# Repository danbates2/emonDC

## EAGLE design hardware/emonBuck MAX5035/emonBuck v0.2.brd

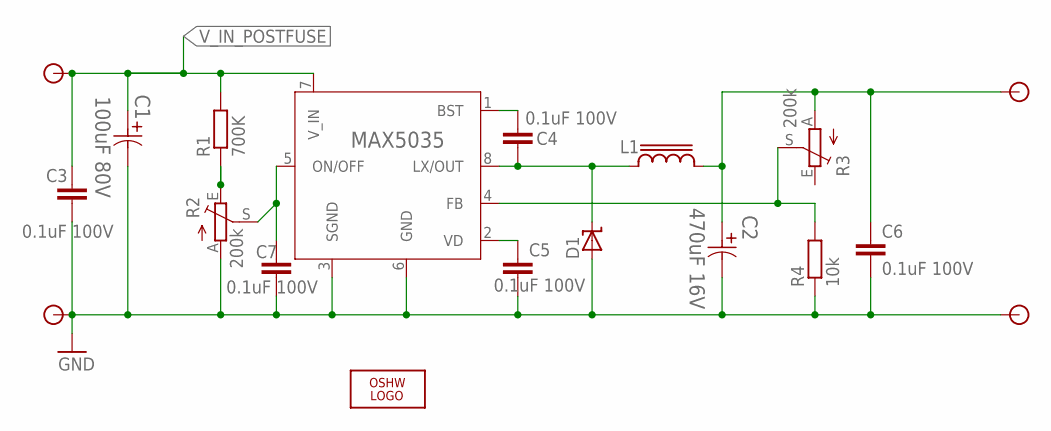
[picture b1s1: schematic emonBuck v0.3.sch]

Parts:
C1: 100uF 80V; CAPAE1350X1400N
C2: 470uF 16V; CAPAE830X1050N
C3, C4, C5, C6, C7: 0.1uF 100V; C0603
D1: MBRS1100T3G; SMB_1; MPN MBRS1100T3G
L1: SRR1208; SSR1208; MPN SRR1208-151YL
LOGO1: OSHW_LOGO_6MILX0200-NT; OSHW_6X200_NOTEXT
MAX5035: MAX5035; 21-0111D_SBE-14; MPN MAX5035EASA+
R1: 700K; R0603
R2, R3: 200k; B64W
R4: 10k; R0603
U$1, U$2, U$3, U$4: TP0.8MM; TP0.8

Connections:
BST: C4.1, MAX5035.1 (BST)
GND: C1.2, C2.2, C3.2, C5.2, C6.2, C7.2, D1.A, MAX5035.3 (SGND), MAX5035.6 (GND), R2.A, R4.1, U$2.P$1, U$4.P$1
LX: C4.2, D1.C, L1.1, MAX5035.8 (LX/OUT)
unnamed: MAX5035.4 (FB), R3.S, R4.2
unnamed: C7.1, MAX5035.5 (ON/OFF), R2.S
unnamed: R1.1, R2.E
PRE_6.5V: C2.1, C6.1, L1.2, R3.A, U$3.P$1
VD: C5.1, MAX5035.2 (VD)
V_IN_POSTFUSE: C1.1, C3.1, MAX5035.7 (V_IN), R1.2, U$1.P$1

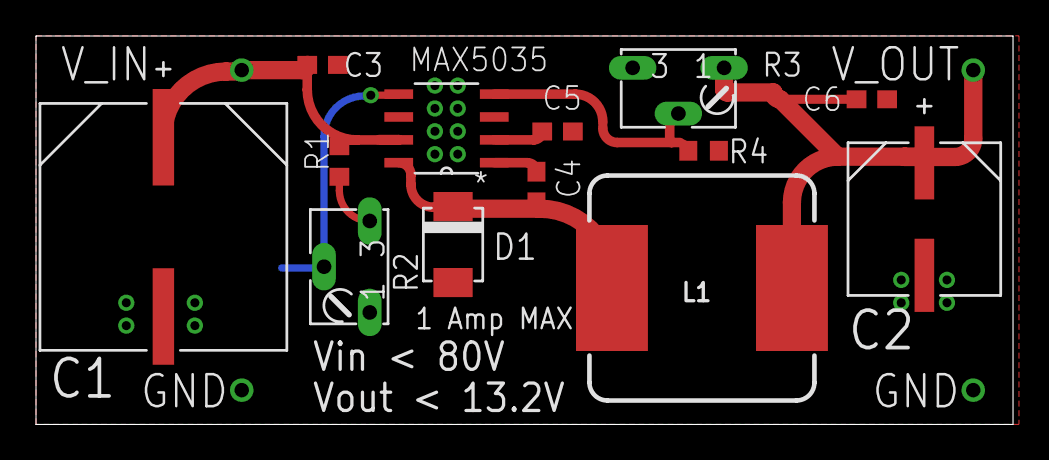
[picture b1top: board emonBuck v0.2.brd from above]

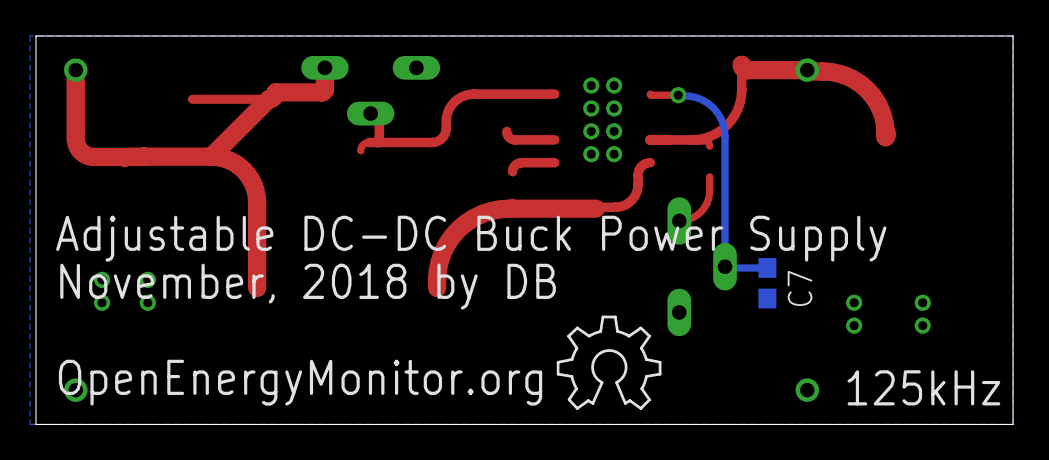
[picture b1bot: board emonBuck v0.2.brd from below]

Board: 2 copper layers, 54.3 x 21.6 mm, 19 parts (2 on the bottom side), 9 nets.

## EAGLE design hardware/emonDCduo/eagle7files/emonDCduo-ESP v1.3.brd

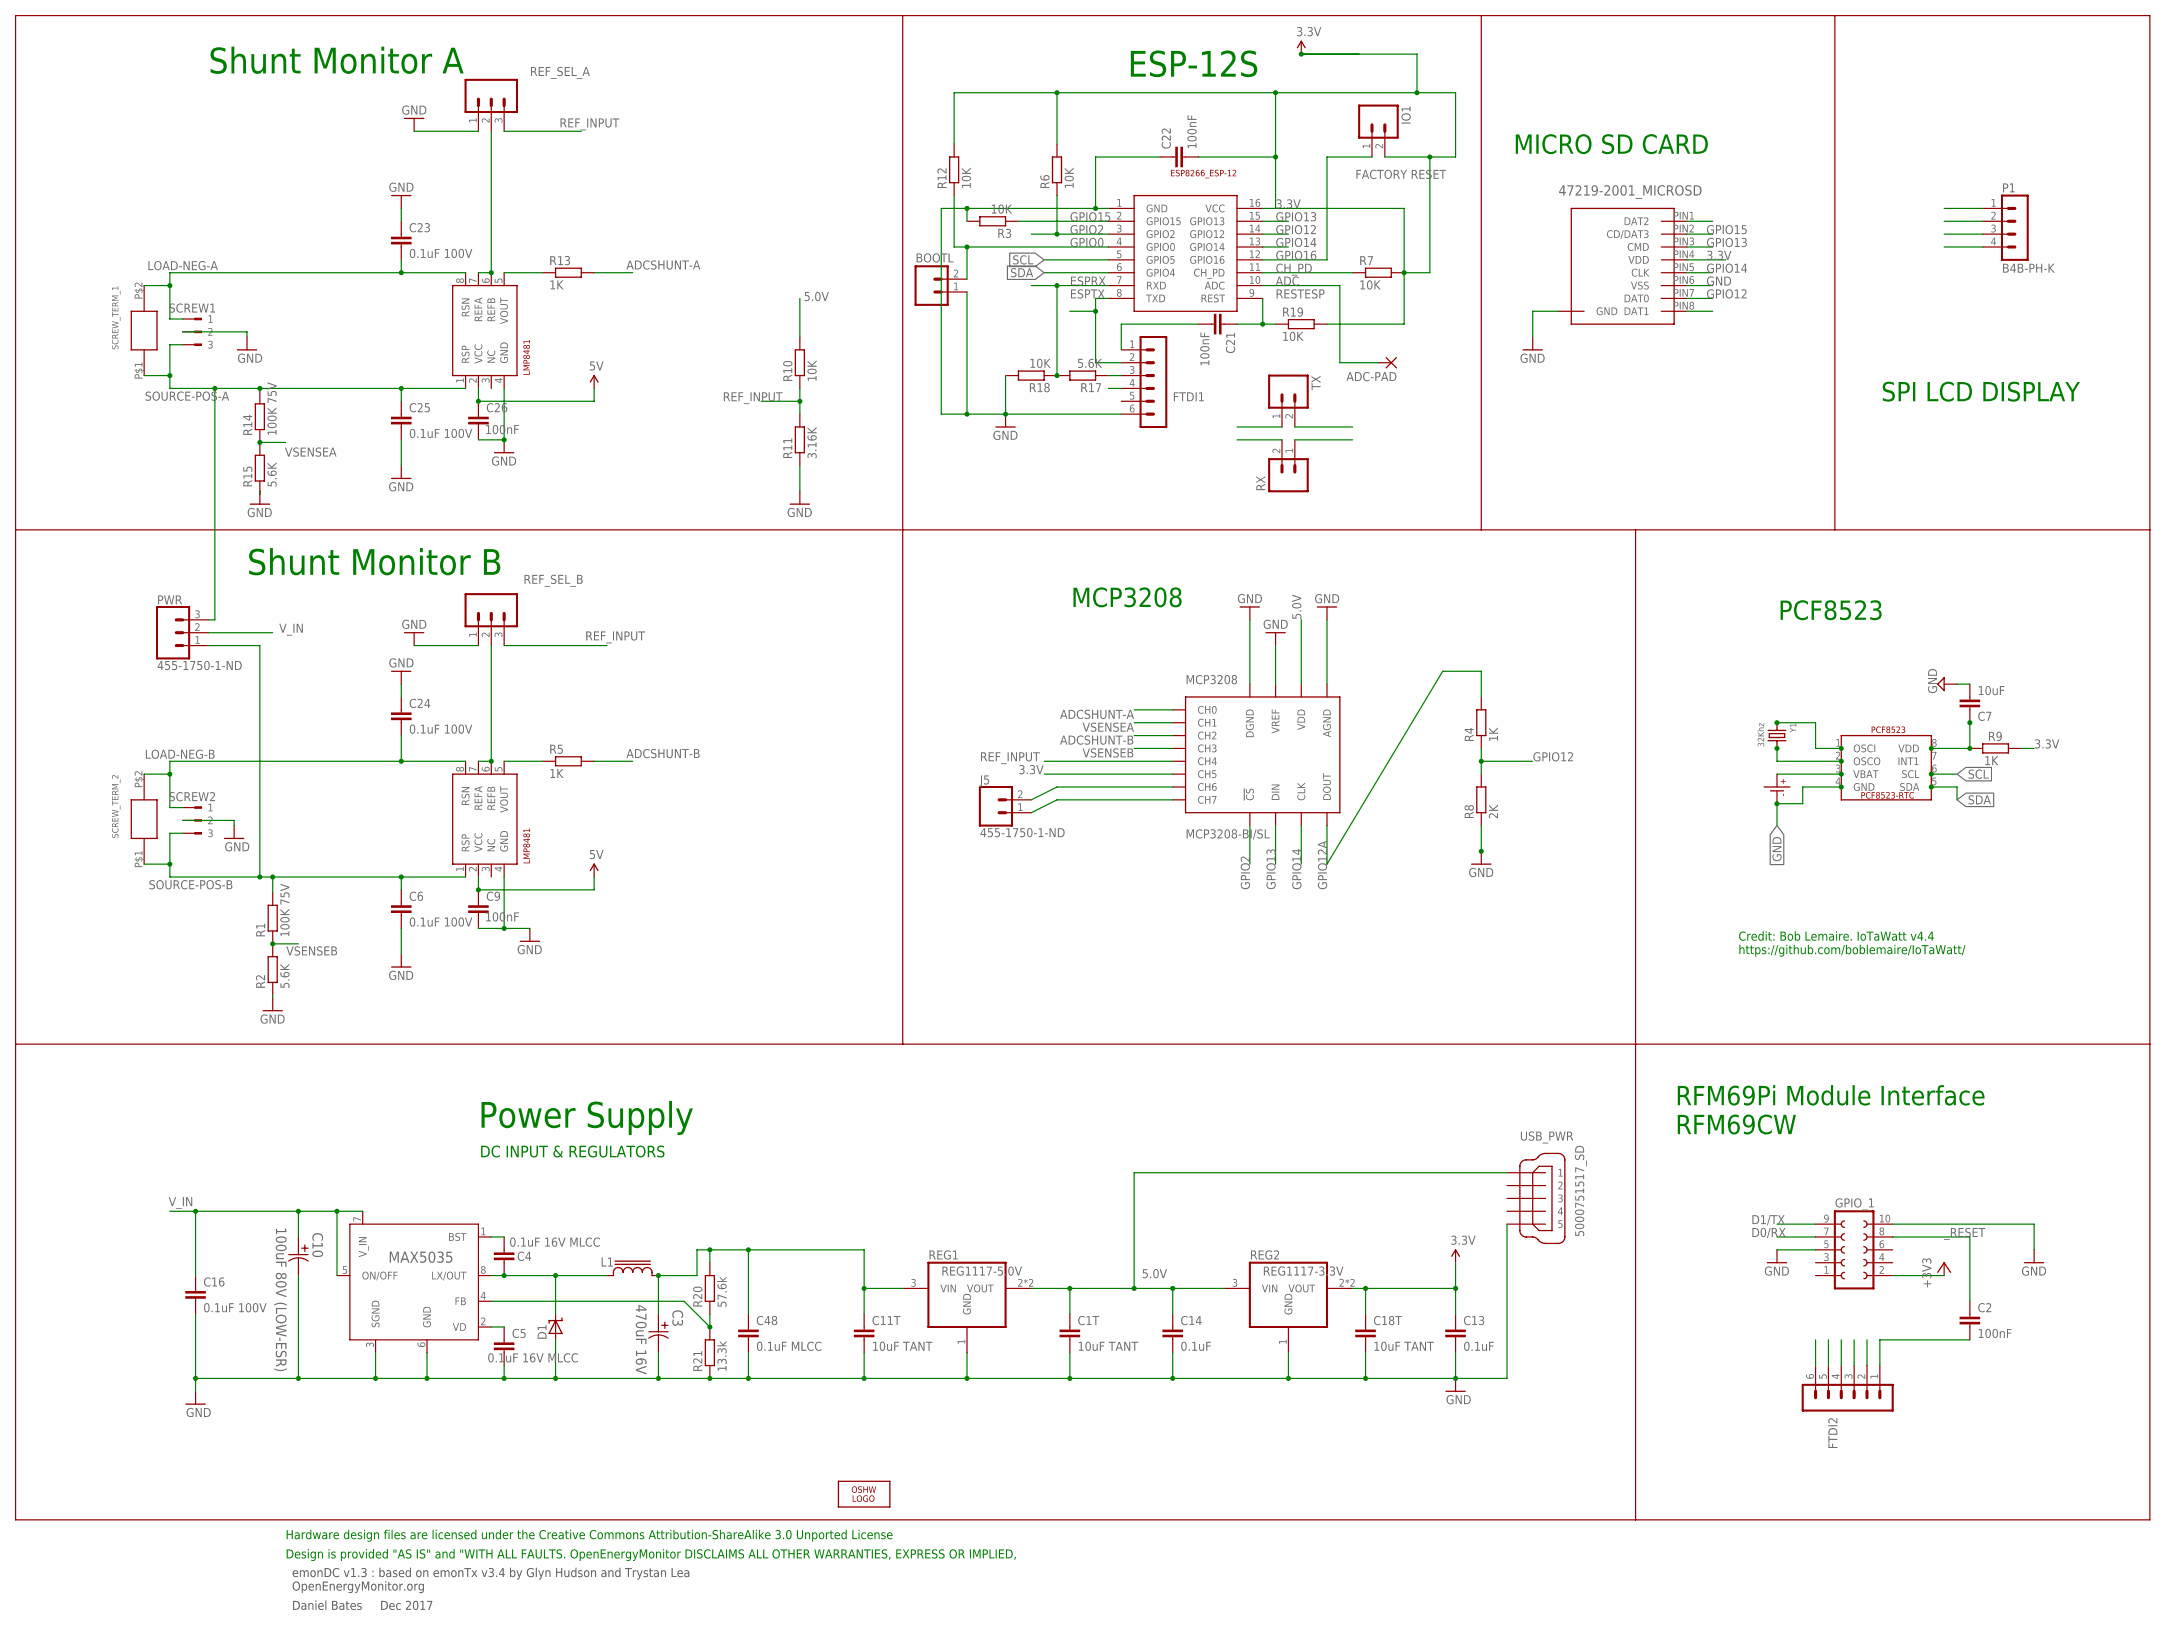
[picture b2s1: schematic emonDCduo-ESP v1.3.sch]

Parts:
ADC-PAD: 2,15/1,0
BOOTL: M02PTH; 1X02
C1T, C11T, C18T: 10uF TANT; C0603
C2, C21, C22: 100nF; C0603
C3: 470uF 16V; CAPAE830X1050N
C4, C5: 0.1uF 16V MLCC; C0603
C6, C23, C24, C25: 0.1uF 100V; C0603; MPN C1608X7S2A104K080AB
C7: 10uF; C0603
C9, C26: 100nF; C0603; MPN C1608X7S2A104K080AB
C10: 100uF 80V (LOW-ESR); CAPAE1350X1400N
C13, C14: 0.1uF; C0603
C16: 0.1uF 100V; C0603
C48: 0.1uF MLCC; C0603
CR1220: CR1220SMD; MPN Harwin S8411-45R
D1: MBRS1100T3G; SMB_1; MPN MBRS1100T3G
ESP-12: ESP8266_ESP-12; ESP8266-ESP12
FTDI1, FTDI2: FTDI; MA06-1
GPIO_1: FE05-2
IO1: M02PTH; 1X02
J5: 455-1750-1-ND; 1X02
L1: SRR1208; SSR1208; MPN SRR1208-151YL
LOGO1: OSHW_LOGO_6MILX0200-NT; OSHW_6X200_NOTEXT
MCP3208: MCP3208-BI/SL; SOIC16
P1: B4B-PH-K
PCF8523: PCF8523_RTC; SOIC_8
PWR: 455-1750-1-ND; 1X03
R1, R14: 100K 75V; R0603; MPN MCWR06X1003FTL
R2, R15: 5.6K; R0603; MPN MCWR06X5901FTL
R3, R6, R7, R12, R18, R19: 10K; R0603
R4: 1K; R0603; MPN MCWR06X5901FTL
R5, R9, R13: 1K; R0603
R8: 2K; R0603; MPN MCWR06X5901FTL
R10: 10K; 0309/12
R11: 3.16K; 0309/12
R17: 5.6K; R0603
R20: 57.6k; R0603
R21: 13.3k; R0603
REF_SEL_A: 455-1750-1-ND; 1X03; MPN 2212S-02SG-85
REF_SEL_B: 455-1750-1-ND; 1X03; MPN 2212S-02SG-85
REG0: MAX5035; 21-0111D_SBE-14; MPN MAX5035EASA+
REG1: REG1117-5.0V; SOT223; MPN REG1117-5.0
REG2: REG1117-3.3V; SOT223; MPN REG1117-3.3
RX: M02PTH; 1X02
SCREW1, SCREW2: 180-3
SCREW_TERM_1, SCREW_TERM_2: EBW_SERIES_15.2MM
SHUNTMON-A: LMP8481; S-PDSO-G08; MPN LMP8481MME-S/NOPB
SHUNTMON-B: LMP8481; S-PDSO-G08; MPN LMP8481MME-H/NOPB
TX: M02PTH; 1X02
U$4: 47219-2001_MICROSD
USB_PWR: 5000751517_SD
Y1: 32Khz; CRYSTAL_8X3.8

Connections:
3.3V: C13.1, C18T.1, C22.2, ESP-12.16 (VCC), GPIO_1.2, IO1.2, MCP3208.6 (CH5), P1.3, R6.2, R7.2, R9.2, R12.2, R19.2, REG2.2 (VOUT), REG2.4 (VOUT), U$4.PIN4 (VDD)
5.0V: C1T.1, C9.1, C14.1, C26.1, FTDI1.4, FTDI2.4, MCP3208.16 (VDD), R10.2, REG1.2 (VOUT), REG1.4 (VOUT), REG2.3 (VIN), SHUNTMON-A.2 (VCC), SHUNTMON-B.2 (VCC), USB_PWR.VBUS (1)
6.5V: C3.1, C11T.1, C48.1, L1.2, R20.2, REG1.3 (VIN)
ADC: ADC-PAD.1, ESP-12.10 (ADC)
ADCSHUNT-A: MCP3208.1 (CH0), R13.2
ADCSHUNT-B: MCP3208.3 (CH2), R5.2
BST: C4.1, REG0.1 (BST)
CH6: J5.2, MCP3208.7 (CH6)
CH7: J5.1, MCP3208.8 (CH7)
CH_PD: ESP-12.11 (CH_PD), R7.1
D0/RX: FTDI2.2, GPIO_1.7, TX.2
D1/TX: FTDI2.3, GPIO_1.9, RX.1
ESPRX: ESP-12.7 (RXD), R17.2, R18.1, RX.2
ESPTX: ESP-12.8 (TXD), FTDI1.2, TX.1
FB: R20.1, R21.2, REG0.4 (FB)
GND: BOOTL.1, C1T.2, C3.2, C5.2, C6.2, C7.2, C9.2, C10.2, C11T.2, C13.2, C14.2, C16.2, C18T.2, C22.1, C23.1, C24.1, C25.2, C26.2, C48.2, CR1220.P- (P$-), D1.A, ESP-12.1 (GND), FTDI1.6, FTDI2.6, GPIO_1.5, GPIO_1.10, MCP3208.9 (DGND), MCP3208.14 (AGND), MCP3208.15 (VREF), P1.4, PCF8523.4 (GND), R2.1, R3.2, R8.1, R11.1, R15.1, R18.2, R21.1, REF_SEL_A.1, REF_SEL_B.1, REG0.3 (SGND), REG0.6 (GND), REG1.1 (GND), REG2.1 (GND), SCREW1.2, SCREW2.2, SHUNTMON-A.4 (GND), SHUNTMON-B.4 (GND), U$4.P$1 (GND), U$4.P$2 (GND), U$4.P$3 (GND), U$4.P$4 (GND), U$4.PIN6 (VSS), USB_PWR.GND1 (5), USB_PWR.GND2 (5), USB_PWR.GND3 (5)
GPIO0: BOOTL.2, ESP-12.4 (GPIO0), R12.1
GPIO2: ESP-12.3 (GPIO2), MCP3208.10 (!CS), R6.1
GPIO12: ESP-12.14 (GPIO12), R4.1, R8.2, U$4.PIN7 (DAT0)
GPIO12A: MCP3208.12 (DOUT), R4.2
GPIO13: ESP-12.15 (GPIO13), MCP3208.11 (DIN), U$4.PIN3 (CMD)
GPIO14: ESP-12.13 (GPIO14), MCP3208.13 (CLK), U$4.PIN5 (CLK)
GPIO15: ESP-12.2 (GPIO15), R3.1, U$4.PIN2 (CD/DAT3)
GPIO16: ESP-12.12 (GPIO16), IO1.1
LOAD-NEG-A: C23.2, SCREW1.1, SCREW_TERM_1.P$2, SHUNTMON-A.8 (RSN)
LOAD-NEG-B: C24.2, SCREW2.1, SCREW_TERM_2.P$2, SHUNTMON-B.8 (RSN)
LX: C4.2, D1.C, L1.1, REG0.8 (LX/OUT)
unnamed: R13.1, SHUNTMON-A.5 (VOUT)
unnamed: R5.1, SHUNTMON-B.5 (VOUT)
unnamed: C7.1, PCF8523.8 (VDD), R9.1
unnamed: C21.2, FTDI1.1
unnamed: FTDI1.3, R17.1
unnamed: CR1220.P+ (P$+), PCF8523.3 (VBAT)
unnamed: PCF8523.2 (OSCO), Y1.P$4 (2)
unnamed: PCF8523.1 (OSCI), Y1.P$1 (1)
unnamed: C2.2, FTDI2.1
REF_A_INPUT: REF_SEL_A.2, SHUNTMON-A.6 (REFB), SHUNTMON-A.7 (REFA)
REF_B_INPUT: REF_SEL_B.2, SHUNTMON-B.6 (REFB), SHUNTMON-B.7 (REFA)
REF_INPUT: MCP3208.5 (CH4), R10.1, R11.2, REF_SEL_A.3, REF_SEL_B.3
RESTESP: C21.1, ESP-12.9 (REST), R19.1
SCL: ESP-12.5 (GPIO5), P1.2, PCF8523.6 (SCL)
SDA: ESP-12.6 (GPIO4), P1.1, PCF8523.5 (SDA)
SOURCE-POS-A: C25.1, PWR.3, R14.2, SCREW1.3, SCREW_TERM_1.P$1, SHUNTMON-A.1 (RSP)
SOURCE-POS-B: C6.1, PWR.1, R1.2, SCREW2.3, SCREW_TERM_2.P$1, SHUNTMON-B.1 (RSP)
VD: C5.1, REG0.2 (VD)
VSENSEA: MCP3208.2 (CH1), R14.1, R15.2
VSENSEB: MCP3208.4 (CH3), R1.1, R2.2
V_IN: C10.1, C16.1, PWR.2, REG0.5 (ON/OFF), REG0.7 (V_IN)
_RESET: C2.1, GPIO_1.8

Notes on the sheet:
emonDC v1.3 : based on emonTx v3.4 by Glyn Hudson and Trystan Lea OpenEnergyMonitor.org
Daniel Bates Dec 2017
Power Supply
Design is provided "AS IS" and "WITH ALL FAULTS. OpenEnergyMonitor DISCLAIMS ALL OTHER WARRANTIES, EXPRESS OR IMPLIED,
Hardware design files are licensed under the Creative Commons Attribution-ShareAlike 3.0 Unported License
DC INPUT & REGULATORS
Shunt Monitor B
Shunt Monitor A
FACTORY RESET
ESP-12S
MICRO SD CARD
RFM69Pi Module Interface RFM69CW
MCP3208
PCF8523
Credit: Bob Lemaire. IoTaWatt v4.4 https://github.com/boblemaire/IoTaWatt/
SPI LCD DISPLAY

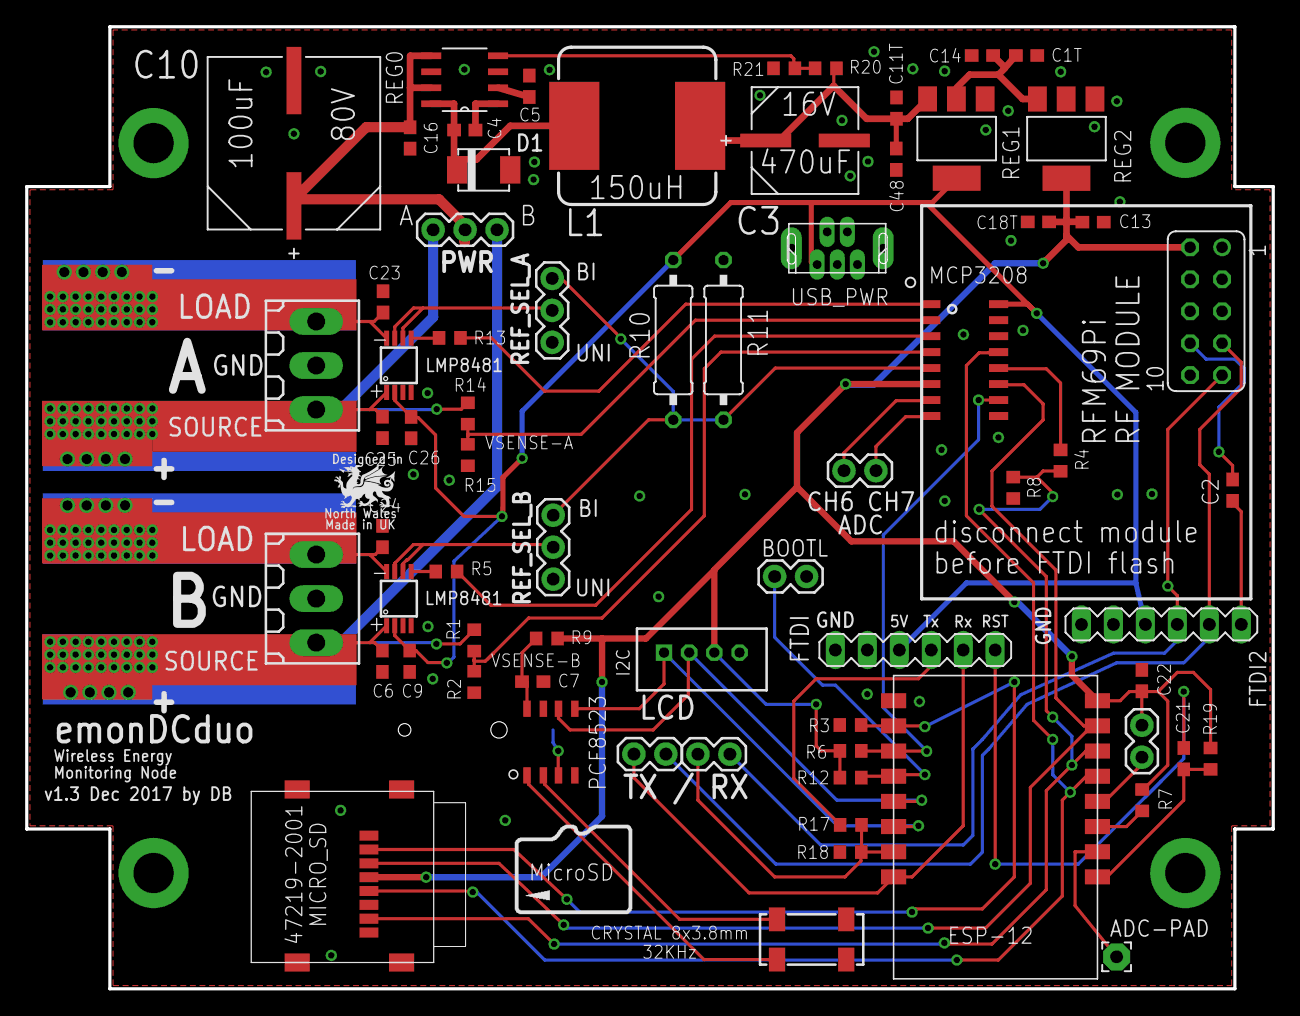
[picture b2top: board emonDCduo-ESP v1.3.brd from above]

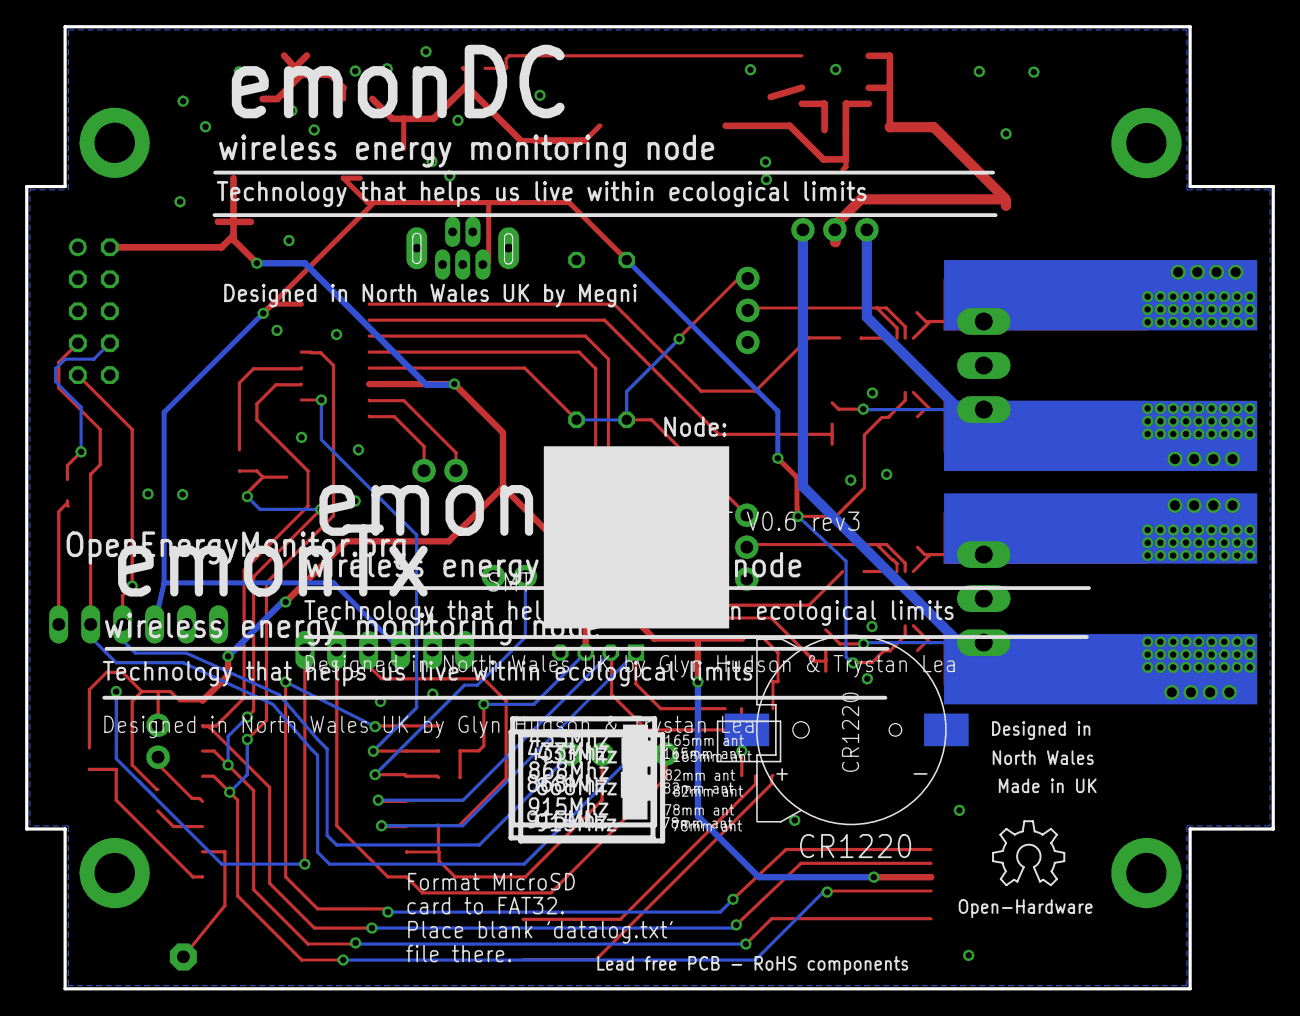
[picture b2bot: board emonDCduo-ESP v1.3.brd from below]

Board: 2 copper layers, 99.1 x 76.5 mm, 73 parts (2 on the bottom side), 49 nets.

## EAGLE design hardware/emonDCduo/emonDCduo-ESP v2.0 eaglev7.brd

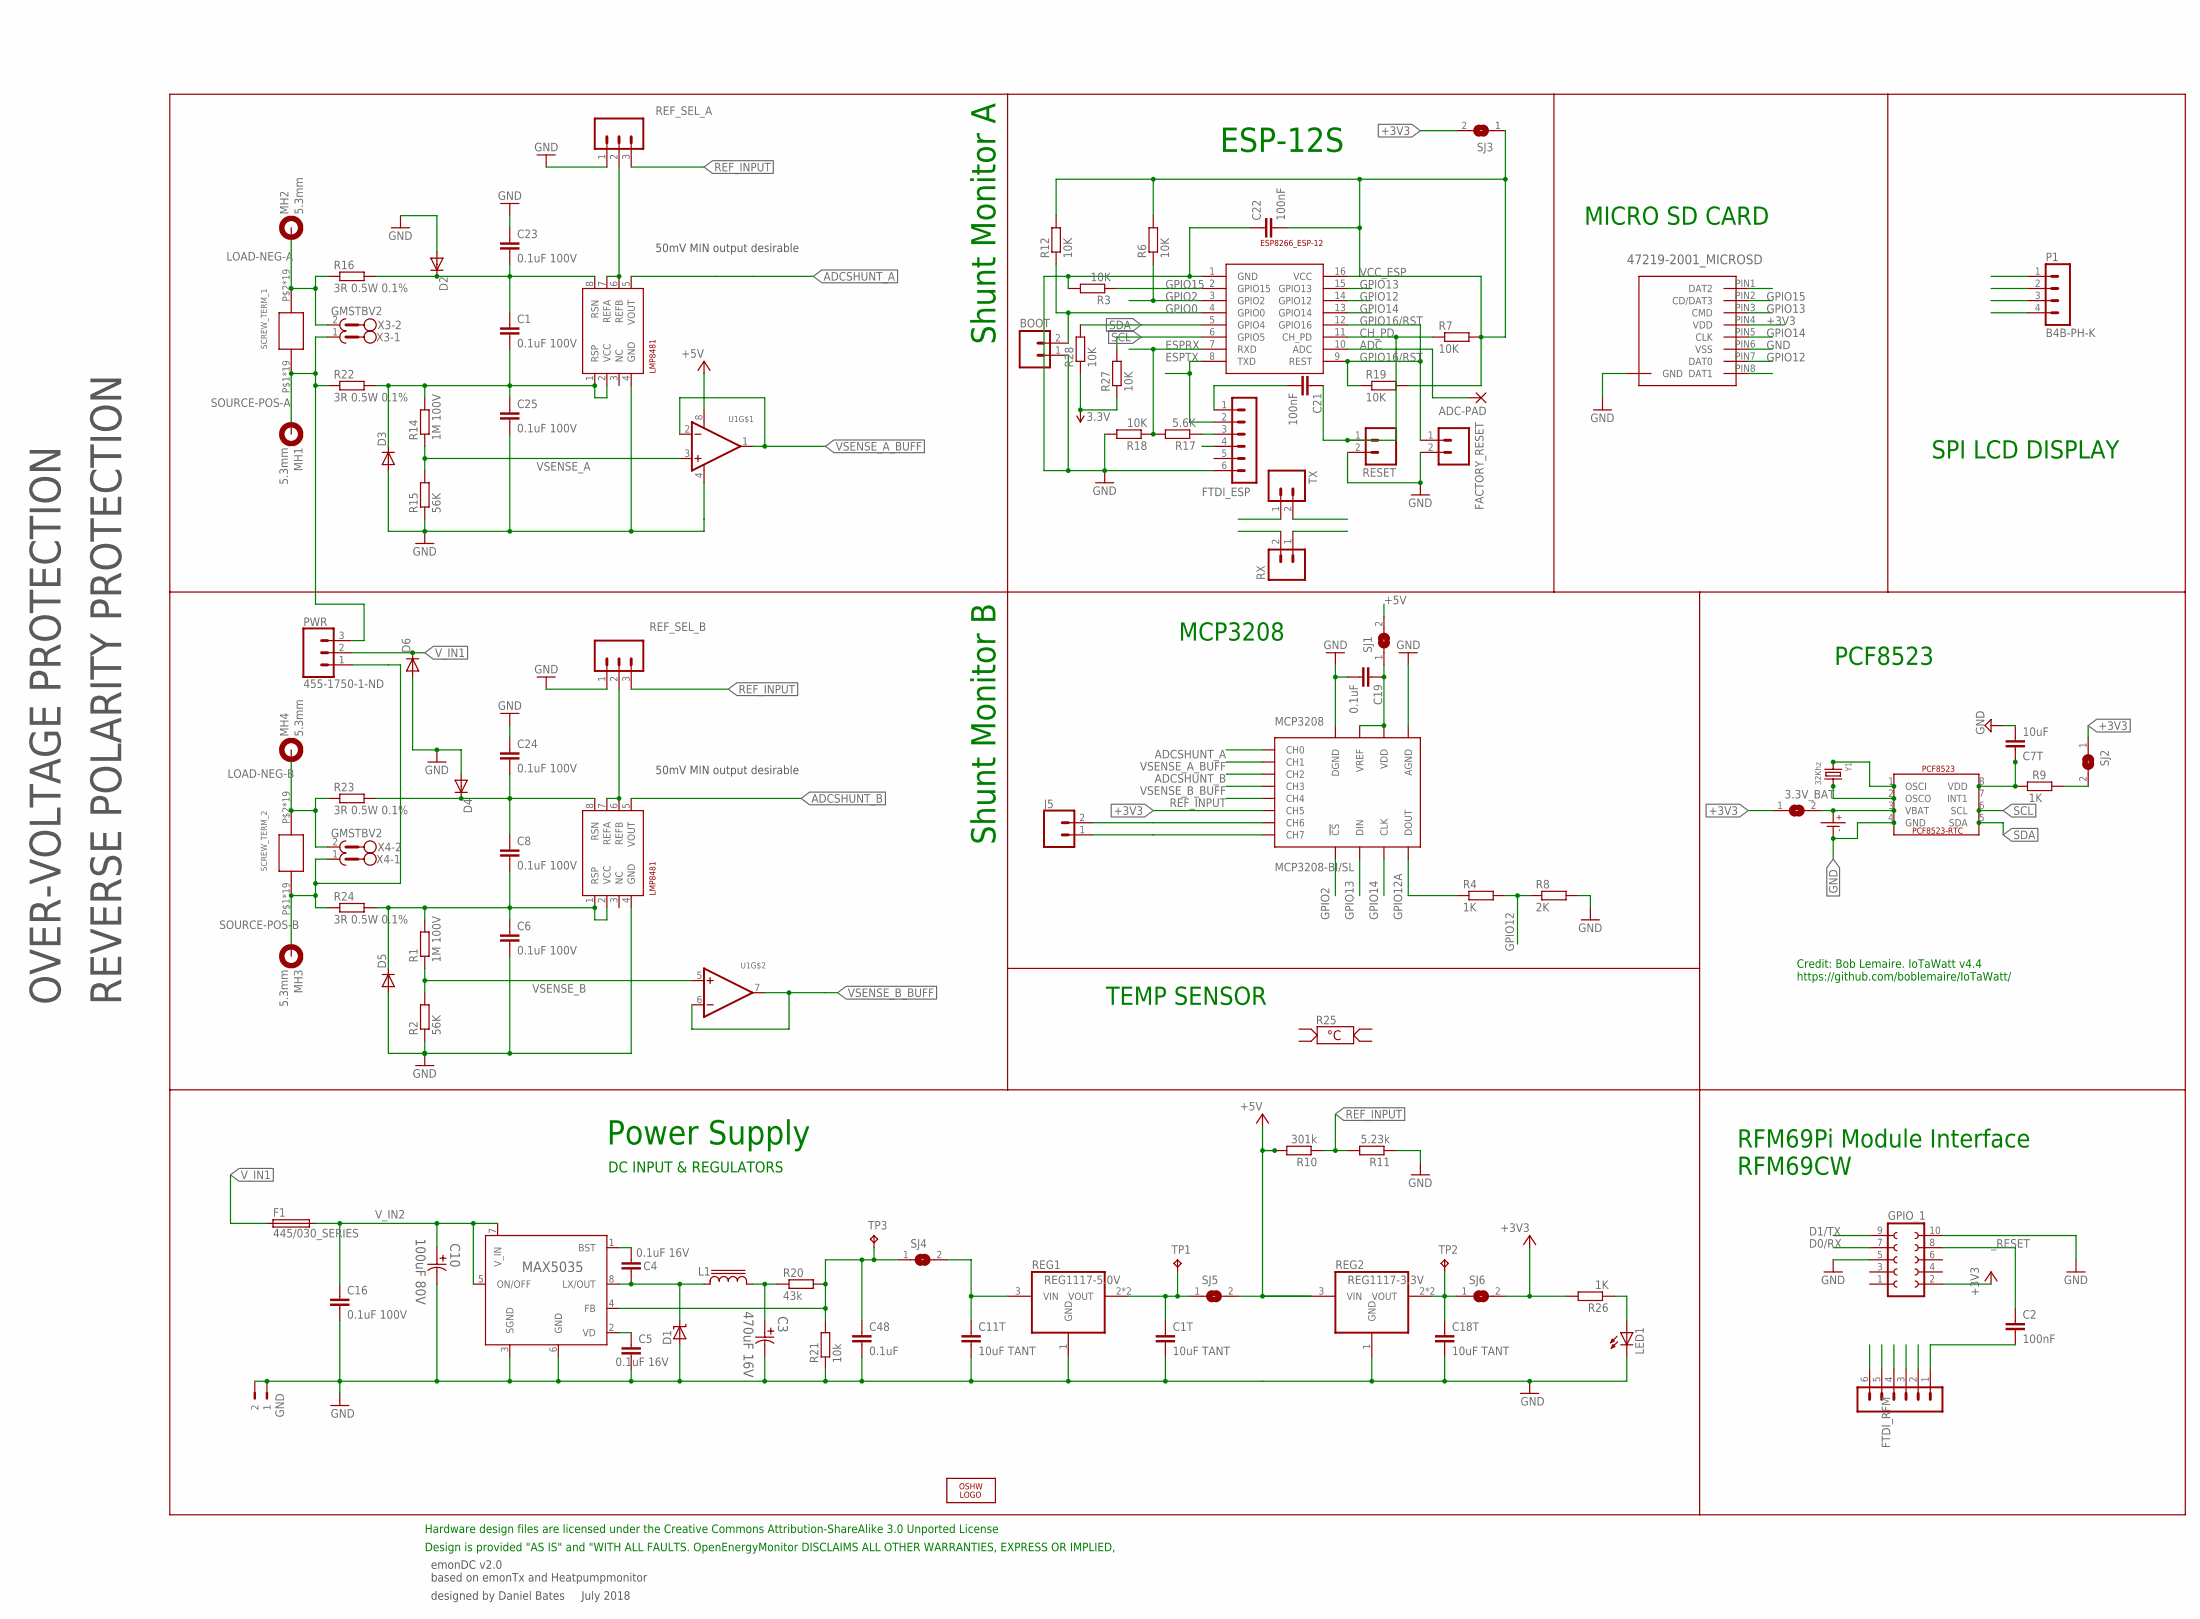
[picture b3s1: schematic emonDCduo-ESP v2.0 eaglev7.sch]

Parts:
3.3V_BAT: SJ-CONCON; SJ-CON
ADC-PAD: 2,15/1,0
BOOT: M02PTH; 1X02
C1, C6, C8, C23, C24, C25: 0.1uF 100V; C0603; MPN C1608X7S2A104K080AB
C1T, C11T, C18T: 10uF TANT; C0603
C2, C21, C22: 100nF; C0603
C3: 470uF 16V; CAPAE830X1050N
C4, C5: 0.1uF 16V; C0603
C7T: 10uF; C0603
C10: 100uF 80V; CAPAE1350X1400N
C16: 0.1uF 100V; C0603
C19, C48: 0.1uF; C0603
CR1220: CR1220SMD; MPN Harwin S8411-45R
D1: MBRS1100T3G; SMB_1; MPN MBRS1100T3G
D2, D3, D4, D5, D6: DIODE-DO214AA; DO214AA
ESP-12: ESP8266_ESP-12; ESP8266-ESP12
F1: 445/030_SERIES; 445/030_SERIES_LITTELFUSE
FACTORY_RESET: FACTORY_RESET; 1X02
FTDI_ESP: FTDI_ESP; MA06-1
FTDI_RFM: FTDI_RFM; MA06-1
GND: 180-2
GPIO_1: FE05-2_RFM69PI_OUTLINERFM69PI; FE05-2_RFM69PI_OULTINE
J5: CONN_02; 1X02
L1: SRR1208; SSR1208; MPN SRR1208-151YL
LED1: LEDCHIP-LED0805; CHIP-LED0805
LOGO1: OSHW_LOGO_6MILX0200-NT; OSHW_6X200_NOTEXT
MCP3208: MCP3208-BI/SL; SOIC16
MH1, MH2, MH3, MH4: 5.3mm; 5,3//11-PAD
MICRO_SD: 47219-2001_MICROSD
P1: B4B-PH-K
PCF8523: PCF8523_RTC; SOIC_8
PWR: 455-1750-1-ND; 1X03
R1, R14: 1M 100V; R0603; MPN MCWR06X1003FTL
R2, R15: 56K; R0603; MPN MCWR06X5901FTL
R3, R6, R7, R12, R18, R19, R27, R28: 10K; R0603
R4: 1K; R0603; MPN MCWR06X5901FTL
R8: 2K; R0603; MPN MCWR06X5901FTL
R9, R26: 1K; R0603
R10: 301k; 0204/7
R11: 5.23k; 0204/7
R16, R22, R23, R24: 3R 0.5W 0.1%; R0805
R17: 5.6K; R0603
R20: 43k; R0603
R21: 10k; R0603
R25: 3220824X; PT1206
REF_SEL_A: 455-1750-1-ND; 1X03; MPN 2212S-02SG-85
REF_SEL_B: 455-1750-1-ND; 1X03; MPN 2212S-02SG-85
REG0: MAX5035; 21-0111D_SBE-14; MPN MAX5035EASA+
REG1: REG1117-5.0V; SOT223; MPN REG1117-5.0
REG2: REG1117-3.3V; SOT223; MPN REG1117-3.3
RESET: M02PTH; 1X02
RX: M02PTH; 1X02
SCREW_TERM_1, SCREW_TERM_2: EBW_SERIES_15.2MM
SHUNTMON-A: LMP8481; S-PDSO-G08; MPN LMP8481MME-S/NOPB
SHUNTMON-B: LMP8481; S-PDSO-G08; MPN LMP8481MME-H/NOPB
SJ1, SJ2, SJ3, SJ4, SJ5, SJ6: SJ-CONCON; SJ-CON
TP1, TP2, TP3: TPPAD1-13; P1-13
TX: M02PTH; 1X02
U1: LM358; SOIC8_150MIL
X3, X4: GMSTBV2
Y1: 32Khz; CRYSTAL_8X3.8

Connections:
3.3V_PRE: C18T.1, REG2.2 (VOUT), REG2.4 (VOUT), SJ6.1, TP2.TP
5V_PRE: C1T.1, REG1.2 (VOUT), REG1.4 (VOUT), SJ5.1, TP1.TP
6.5V: C11T.1, REG1.3 (VIN), SJ4.2
+3V3: 3.3V_BAT.1, GPIO_1.2, MCP3208.6 (CH5), MICRO_SD.PIN4 (VDD), P1.3, R26.2, R27.1, R28.1, SJ2.1, SJ3.2, SJ6.2
+5V: FTDI_ESP.4, FTDI_RFM.4, R10.2, REG2.3 (VIN), SJ1.2, SJ5.2, U1.8 (V+)
ADC: ADC-PAD.1, ESP-12.10 (ADC)
ADCSHUNT_A: MCP3208.1 (CH0), SHUNTMON-A.5 (VOUT)
ADCSHUNT_B: MCP3208.3 (CH2), SHUNTMON-B.5 (VOUT)
BST: C4.1, REG0.1 (BST)
CH6: J5.2, MCP3208.7 (CH6)
CH7: J5.1, MCP3208.8 (CH7)
CH_PD: C21.1, ESP-12.11 (CH_PD), R7.1, RESET.1
D0/RX: FTDI_RFM.2, GPIO_1.7, TX.2
D1/TX: FTDI_RFM.3, GPIO_1.9, RX.1
ESPRX: ESP-12.7 (RXD), R17.2, R18.1, RX.2
ESPTX: ESP-12.8 (TXD), FTDI_ESP.2, TX.1
GND: BOOT.1, C1T.2, C3.2, C5.2, C6.2, C7T.2, C10.2, C11T.2, C16.2, C18T.2, C19.2, C22.1, C23.1, C24.1, C25.2, C48.2, CR1220.P- (P$-), D1.A, D2.A, D3.A, D4.A, D5.A, D6.A, ESP-12.1 (GND), FACTORY_RESET.2, FTDI_ESP.6, FTDI_RFM.6, GND.1, GND.2, GPIO_1.5, GPIO_1.10, LED1.C, MCP3208.9 (DGND), MCP3208.14 (AGND), MICRO_SD.P$1 (GND), MICRO_SD.P$2 (GND), MICRO_SD.P$3 (GND), MICRO_SD.P$4 (GND), MICRO_SD.PIN6 (VSS), P1.4, PCF8523.4 (GND), R2.1, R3.2, R8.2, R11.1, R15.1, R18.2, R21.1, REF_SEL_A.1, REF_SEL_B.1, REG0.3 (SGND), REG0.6 (GND), REG1.1 (GND), REG2.1 (GND), RESET.2, SHUNTMON-A.4 (GND), SHUNTMON-B.4 (GND), U1.4 (V-)
GPIO0: BOOT.2, ESP-12.4 (GPIO0), R12.1
GPIO2: ESP-12.3 (GPIO2), MCP3208.10 (!CS), R6.1
GPIO12: ESP-12.14 (GPIO12), MICRO_SD.PIN7 (DAT0), R4.2, R8.1
GPIO12A: MCP3208.12 (DOUT), R4.1
GPIO13: ESP-12.15 (GPIO13), MCP3208.11 (DIN), MICRO_SD.PIN3 (CMD)
GPIO14: ESP-12.13 (GPIO14), MCP3208.13 (CLK), MICRO_SD.PIN5 (CLK)
GPIO15: ESP-12.2 (GPIO15), MICRO_SD.PIN2 (CD/DAT3), R3.1
GPIO16/RST: ESP-12.9 (REST), ESP-12.12 (GPIO16), FACTORY_RESET.1, R19.1
LOAD-NEG-A: MH2.B5,5, R16.1, SCREW_TERM_1.P$2, SCREW_TERM_1.P$18, SCREW_TERM_1.P$19, SCREW_TERM_1.P$20, SCREW_TERM_1.P$21, SCREW_TERM_1.P$22, SCREW_TERM_1.P$23, SCREW_TERM_1.P$24, SCREW_TERM_1.P$25, SCREW_TERM_1.P$26, SCREW_TERM_1.P$27, SCREW_TERM_1.P$28, SCREW_TERM_1.P$29, SCREW_TERM_1.P$30, SCREW_TERM_1.P$31, SCREW_TERM_1.P$32, SCREW_TERM_1.P$36, SCREW_TERM_1.P$37, SCREW_TERM_1.P$38, X3.2
LOAD-NEG-B: MH4.B5,5, R23.1, SCREW_TERM_2.P$2, SCREW_TERM_2.P$18, SCREW_TERM_2.P$19, SCREW_TERM_2.P$20, SCREW_TERM_2.P$21, SCREW_TERM_2.P$22, SCREW_TERM_2.P$23, SCREW_TERM_2.P$24, SCREW_TERM_2.P$25, SCREW_TERM_2.P$26, SCREW_TERM_2.P$27, SCREW_TERM_2.P$28, SCREW_TERM_2.P$29, SCREW_TERM_2.P$30, SCREW_TERM_2.P$31, SCREW_TERM_2.P$32, SCREW_TERM_2.P$36, SCREW_TERM_2.P$37, SCREW_TERM_2.P$38, X4.2
LX: C4.2, D1.C, L1.1, REG0.8 (LX/OUT)
MCP_VCC: C19.1, MCP3208.15 (VREF), MCP3208.16 (VDD), SJ1.1
unnamed: LED1.A, R26.1
unnamed: C7T.1, PCF8523.8 (VDD), R9.1
unnamed: C1.1, C23.2, D2.C, R16.2, SHUNTMON-A.8 (RSN)
unnamed: C8.1, C24.2, D4.C, R23.2, SHUNTMON-B.8 (RSN)
unnamed: C1.2, C25.1, D3.C, R14.2, R22.2, SHUNTMON-A.1 (RSP), SHUNTMON-A.2 (VCC)
unnamed: R9.2, SJ2.2
unnamed: C3.1, L1.2, R20.1
unnamed: C21.2, FTDI_ESP.1
unnamed: FTDI_ESP.3, R17.1
unnamed: PCF8523.2 (OSCO), Y1.P$4 (2)
unnamed: PCF8523.1 (OSCI), Y1.P$1 (1)
unnamed: C2.2, FTDI_RFM.1
PRE_6.5V: C48.1, R20.2, R21.2, REG0.4 (FB), SJ4.1, TP3.TP
REF_A_INPUT: REF_SEL_A.2, SHUNTMON-A.6 (REFB), SHUNTMON-A.7 (REFA)
REF_B_INPUT: REF_SEL_B.2, SHUNTMON-B.6 (REFB), SHUNTMON-B.7 (REFA)
REF_INPUT: MCP3208.5 (CH4), R10.1, R11.2, REF_SEL_A.3, REF_SEL_B.3
SCL: ESP-12.6 (GPIO5), P1.2, PCF8523.6 (SCL), R27.2
SDA: ESP-12.5 (GPIO4), P1.1, PCF8523.5 (SDA), R28.2
SOURCE-POS-A: MH1.B5,5, PWR.3, R22.1, SCREW_TERM_1.P$1, SCREW_TERM_1.P$3, SCREW_TERM_1.P$4, SCREW_TERM_1.P$5, SCREW_TERM_1.P$6, SCREW_TERM_1.P$7, SCREW_TERM_1.P$8, SCREW_TERM_1.P$9, SCREW_TERM_1.P$10, SCREW_TERM_1.P$11, SCREW_TERM_1.P$12, SCREW_TERM_1.P$13, SCREW_TERM_1.P$14, SCREW_TERM_1.P$15, SCREW_TERM_1.P$16, SCREW_TERM_1.P$17, SCREW_TERM_1.P$33, SCREW_TERM_1.P$34, SCREW_TERM_1.P$35, X3.1
SOURCE-POS-B: MH3.B5,5, PWR.1, R24.1, SCREW_TERM_2.P$1, SCREW_TERM_2.P$3, SCREW_TERM_2.P$4, SCREW_TERM_2.P$5, SCREW_TERM_2.P$6, SCREW_TERM_2.P$7, SCREW_TERM_2.P$8, SCREW_TERM_2.P$9, SCREW_TERM_2.P$10, SCREW_TERM_2.P$11, SCREW_TERM_2.P$12, SCREW_TERM_2.P$13, SCREW_TERM_2.P$14, SCREW_TERM_2.P$15, SCREW_TERM_2.P$16, SCREW_TERM_2.P$17, SCREW_TERM_2.P$33, SCREW_TERM_2.P$34, SCREW_TERM_2.P$35, X4.1
SOURCE-POS-B_T: C6.1, C8.2, D5.C, R1.2, R24.2, SHUNTMON-B.1 (RSP), SHUNTMON-B.2 (VCC)
VBAT: 3.3V_BAT.2, CR1220.P+ (P$+), PCF8523.3 (VBAT)
VCC_ESP: C22.2, ESP-12.16 (VCC), R6.2, R7.2, R12.2, R19.2, SJ3.1
VD: C5.1, REG0.2 (VD)
VSENSE_A: R14.1, R15.2, U1.3 (+IN)
VSENSE_A_BUFF: MCP3208.2 (CH1), U1.1 (OUT), U1.2 (-IN)
VSENSE_B: R1.1, R2.2, U1.5 (+IN)
VSENSE_B_BUFF: MCP3208.4 (CH3), U1.6 (-IN), U1.7 (OUT)
V_IN1: D6.C, F1.P$1 (1), F1.P$2 (1), PWR.2
V_IN2: C10.1, C16.1, F1.P$3 (2), F1.P$4 (2), REG0.5 (ON/OFF), REG0.7 (V_IN)
_RESET: C2.1, GPIO_1.8

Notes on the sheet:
emonDC v2.0 based on emonTx and Heatpumpmonitor
designed by Daniel Bates July 2018
Power Supply
Design is provided "AS IS" and "WITH ALL FAULTS. OpenEnergyMonitor DISCLAIMS ALL OTHER WARRANTIES, EXPRESS OR IMPLIED,
Hardware design files are licensed under the Creative Commons Attribution-ShareAlike 3.0 Unported License
DC INPUT & REGULATORS
Shunt Monitor B
Shunt Monitor A
ESP-12S
MICRO SD CARD
RFM69Pi Module Interface RFM69CW
MCP3208
PCF8523
Credit: Bob Lemaire. IoTaWatt v4.4 https://github.com/boblemaire/IoTaWatt/
SPI LCD DISPLAY
TEMP SENSOR
50mV MIN output desirable
REVERSE POLARITY PROTECTION
OVER-VOLTAGE PROTECTION

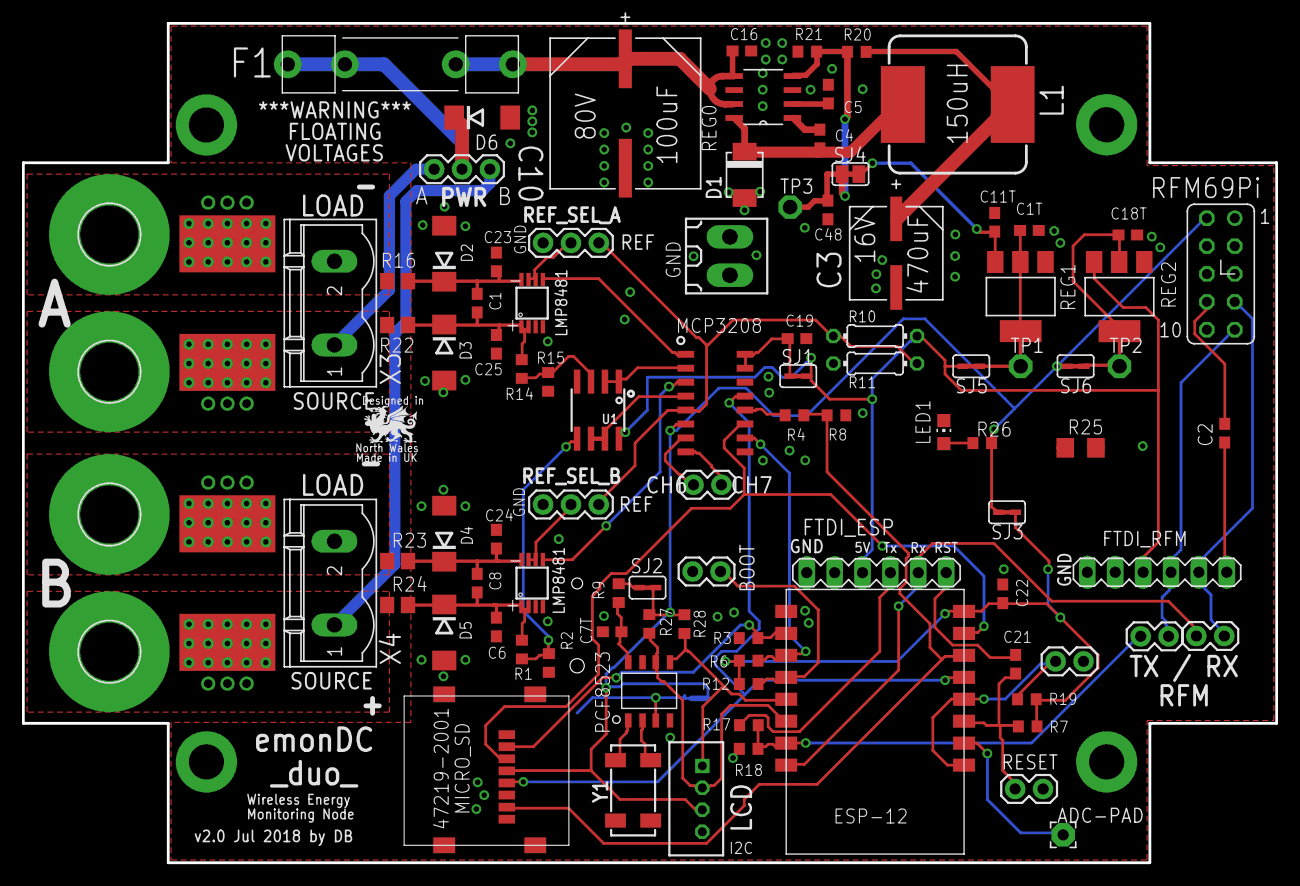
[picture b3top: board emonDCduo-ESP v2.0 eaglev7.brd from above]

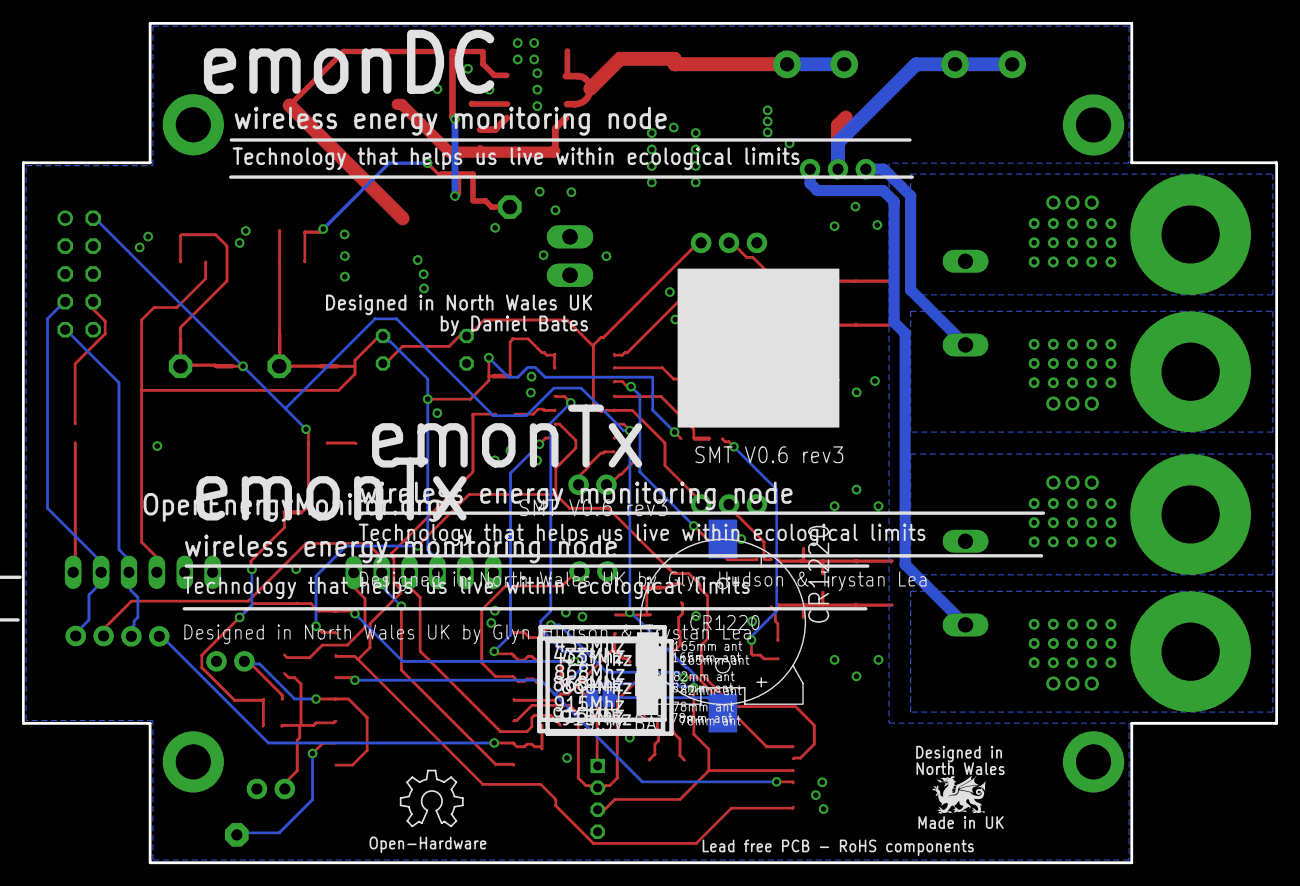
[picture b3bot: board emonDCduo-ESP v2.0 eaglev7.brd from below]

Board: 2 copper layers, 114.2 x 76.5 mm, 102 parts (4 on the bottom side), 60 nets.

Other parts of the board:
U$1: DRAGON_LOGO_NOTEXT

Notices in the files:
parts and their libraries:
inductor-bourns: Copyright (C) 2008, Bob Starr
SparkFun-Connectors: Licensing: CC v3.0 Share-Alike You are welcome to use this library for commercial purposes.
jst-ph: Copyright (C) 2016, Bob Starr
